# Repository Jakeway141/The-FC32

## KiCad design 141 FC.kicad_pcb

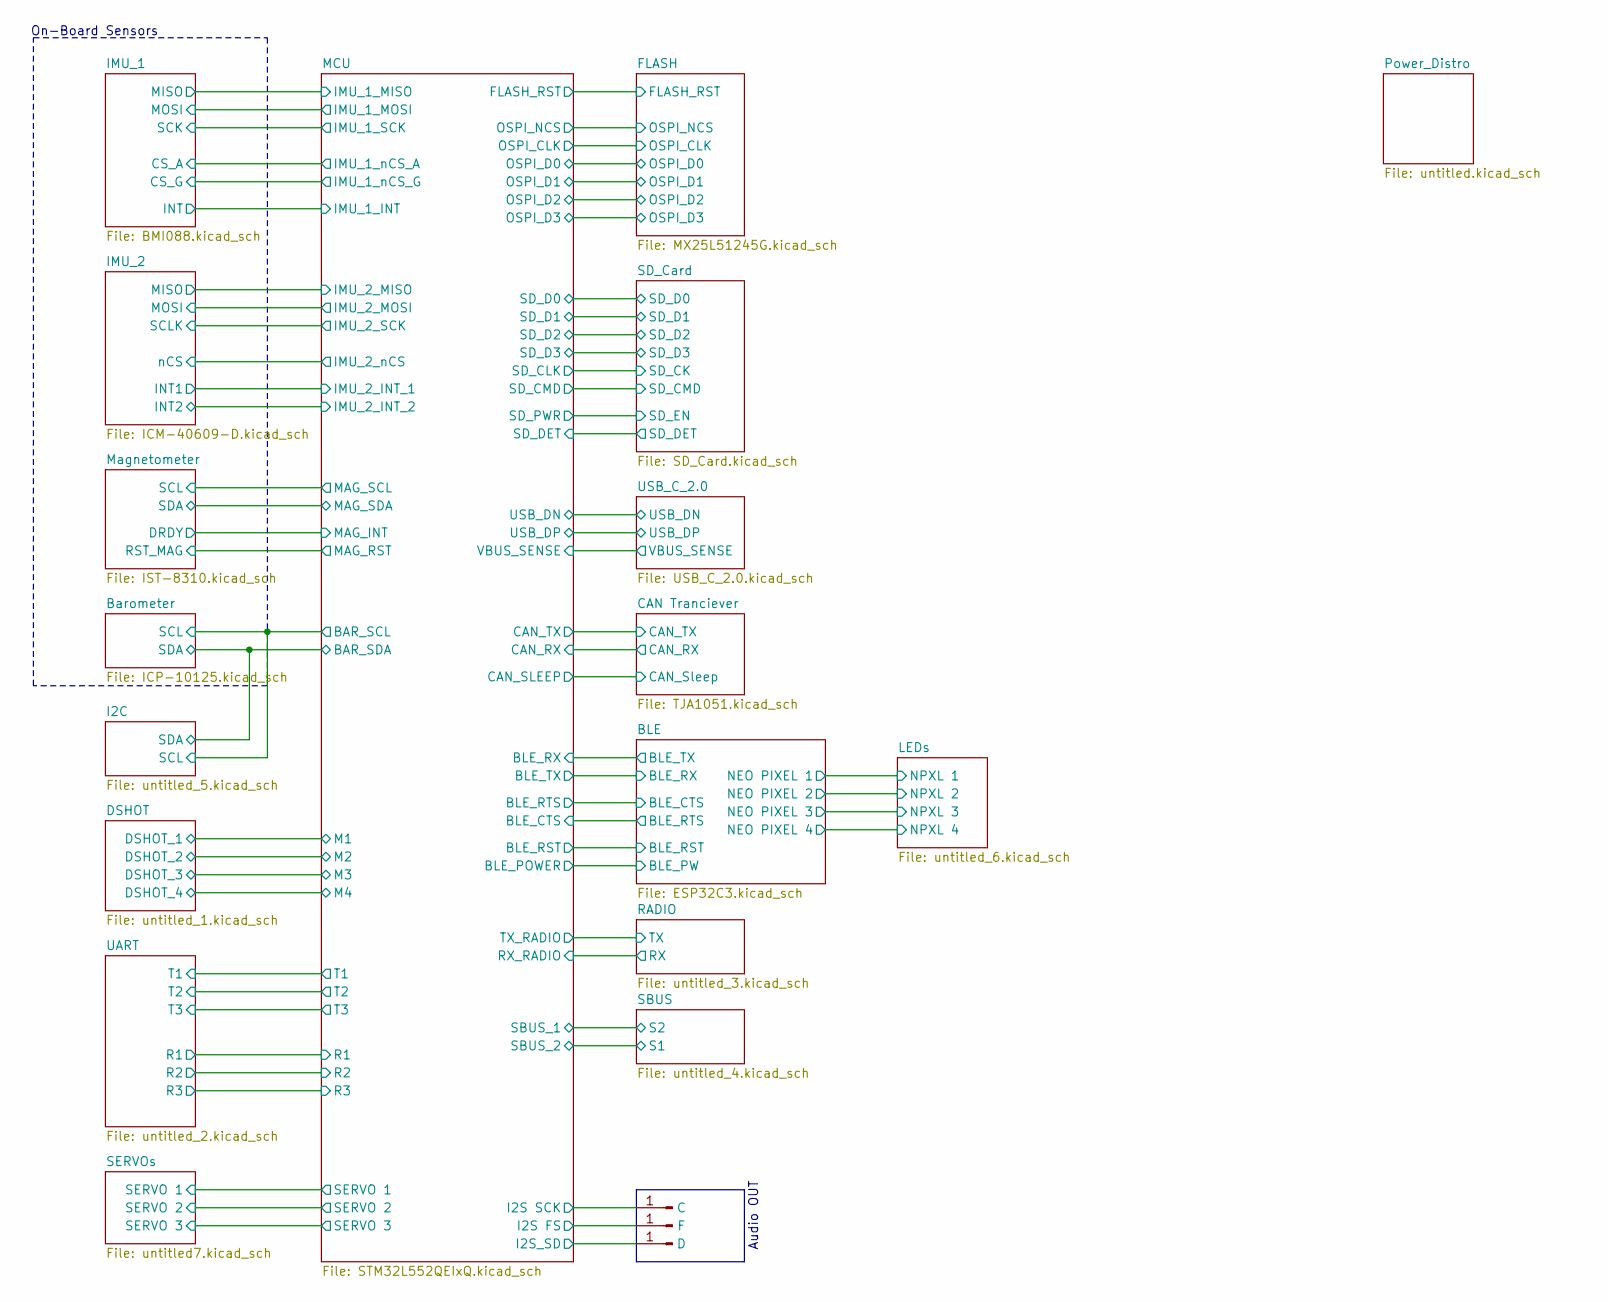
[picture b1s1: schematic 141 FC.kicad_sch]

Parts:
J47: C; SolderWirePad_1x01_SMD_1x2mm
J48: F; SolderWirePad_1x01_SMD_1x2mm
J49: D; SolderWirePad_1x01_SMD_1x2mm

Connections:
/MCU/I2S FS: J48.1 (Pin_1_1); also elsewhere on the board
/MCU/I2S SCK: J47.1 (Pin_1_1); also elsewhere on the board
/MCU/I2S_SD: J49.1 (Pin_1_1); also elsewhere on the board

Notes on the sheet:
Audio OUT
On-Board Sensors

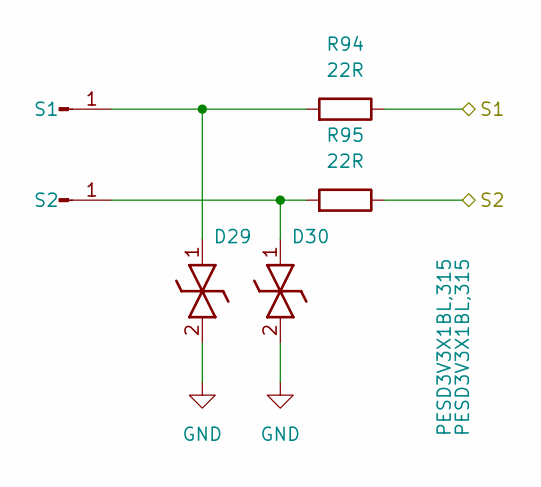
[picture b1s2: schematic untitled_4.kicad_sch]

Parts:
D29, D30: PESD3V3X1BL,315; PESD5V0S1BL315; Manufacturer_Part_Number PESD3V3X1BL,315; Mouser Part Number 771-PESD3V3X1BL,315
J59: S1; SolderWirePad_1x01_SMD_1x2mm
J60: S2; SolderWirePad_1x01_SMD_1x2mm
R94, R95: 22R; R_0805_2012Metric

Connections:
/MCU/SBUS_1: R95.1; also elsewhere on the board
/MCU/SBUS_2: R94.1; also elsewhere on the board
unnamed: D29.1 (K1), J59.1 (Pin_1_1), R94.2
unnamed: D30.1 (K1), J60.1 (Pin_1_1), R95.2

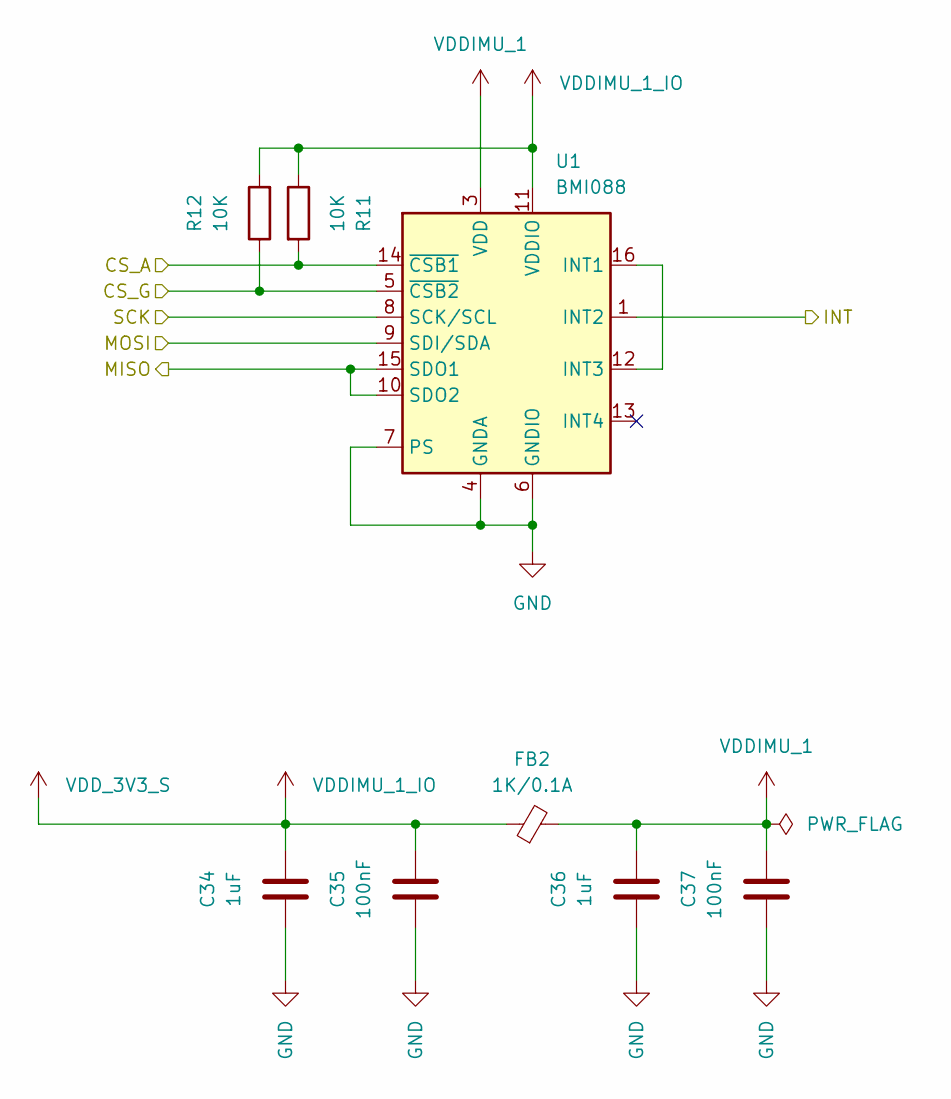
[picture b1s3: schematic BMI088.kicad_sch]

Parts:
C34, C36: 1uF; C_0603_1608Metric
C35, C37: 100nF; C_0603_1608Metric
FB2: 1K/0.1A; L_0603_1608Metric
R11, R12: 10K; R_0603_1608Metric
U1: BMI088; Bosch_LGA-16_4.5x3mm_P0.5mm_LayoutBorder7x1y_ClockwisePinNu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

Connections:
/IMU_1/CS_A: R11.2, U1.14 (~CSB1); also elsewhere on the board
/IMU_1/CS_G: R12.1, U1.5 (~CSB2); also elsewhere on the board
/IMU_1/INT: U1.1 (INT2); also elsewhere on the board
/IMU_1/MISO: U1.10 (SDO2), U1.15 (SDO1); also elsewhere on the board
/IMU_1/MOSI: U1.9 (SDI/SDA); also elsewhere on the board
/IMU_1/SCK: U1.8 (SCK/SCL); also elsewhere on the board
unnamed: U1.12 (INT3), U1.16 (INT1)
VDDIMU_1: C36.2, C37.2, FB2.2, U1.3 (VDD)
VDDIMU_1_IO: C34.2, C35.2, FB2.1, R11.1, R12.2, U1.11 (VDDIO); also elsewhere on the board

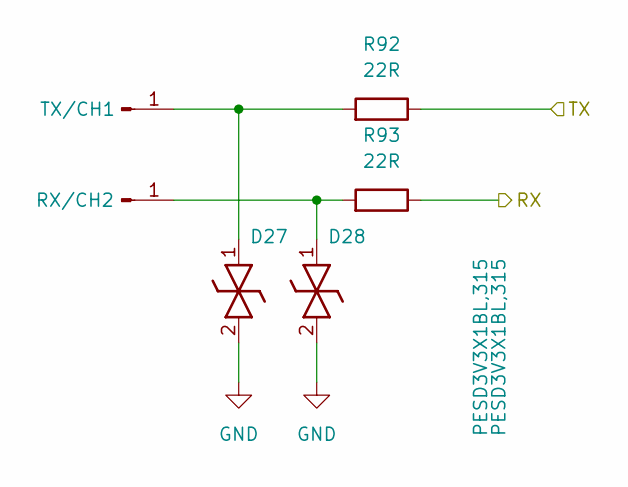
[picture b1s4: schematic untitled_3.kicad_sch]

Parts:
D27, D28: PESD3V3X1BL,315; PESD5V0S1BL315; Manufacturer_Part_Number PESD3V3X1BL,315; Mouser Part Number 771-PESD3V3X1BL,315
J61: TX/CH1; SolderWirePad_1x01_SMD_1x2mm
J62: RX/CH2; SolderWirePad_1x01_SMD_1x2mm
R92, R93: 22R; R_0805_2012Metric

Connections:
/MCU/RX_RADIO: R93.1; also elsewhere on the board
/MCU/TX_RADIO: R92.1; also elsewhere on the board
unnamed: D27.1 (K1), J61.1 (Pin_1_1), R92.2
unnamed: D28.1 (K1), J62.1 (Pin_1_1), R93.2

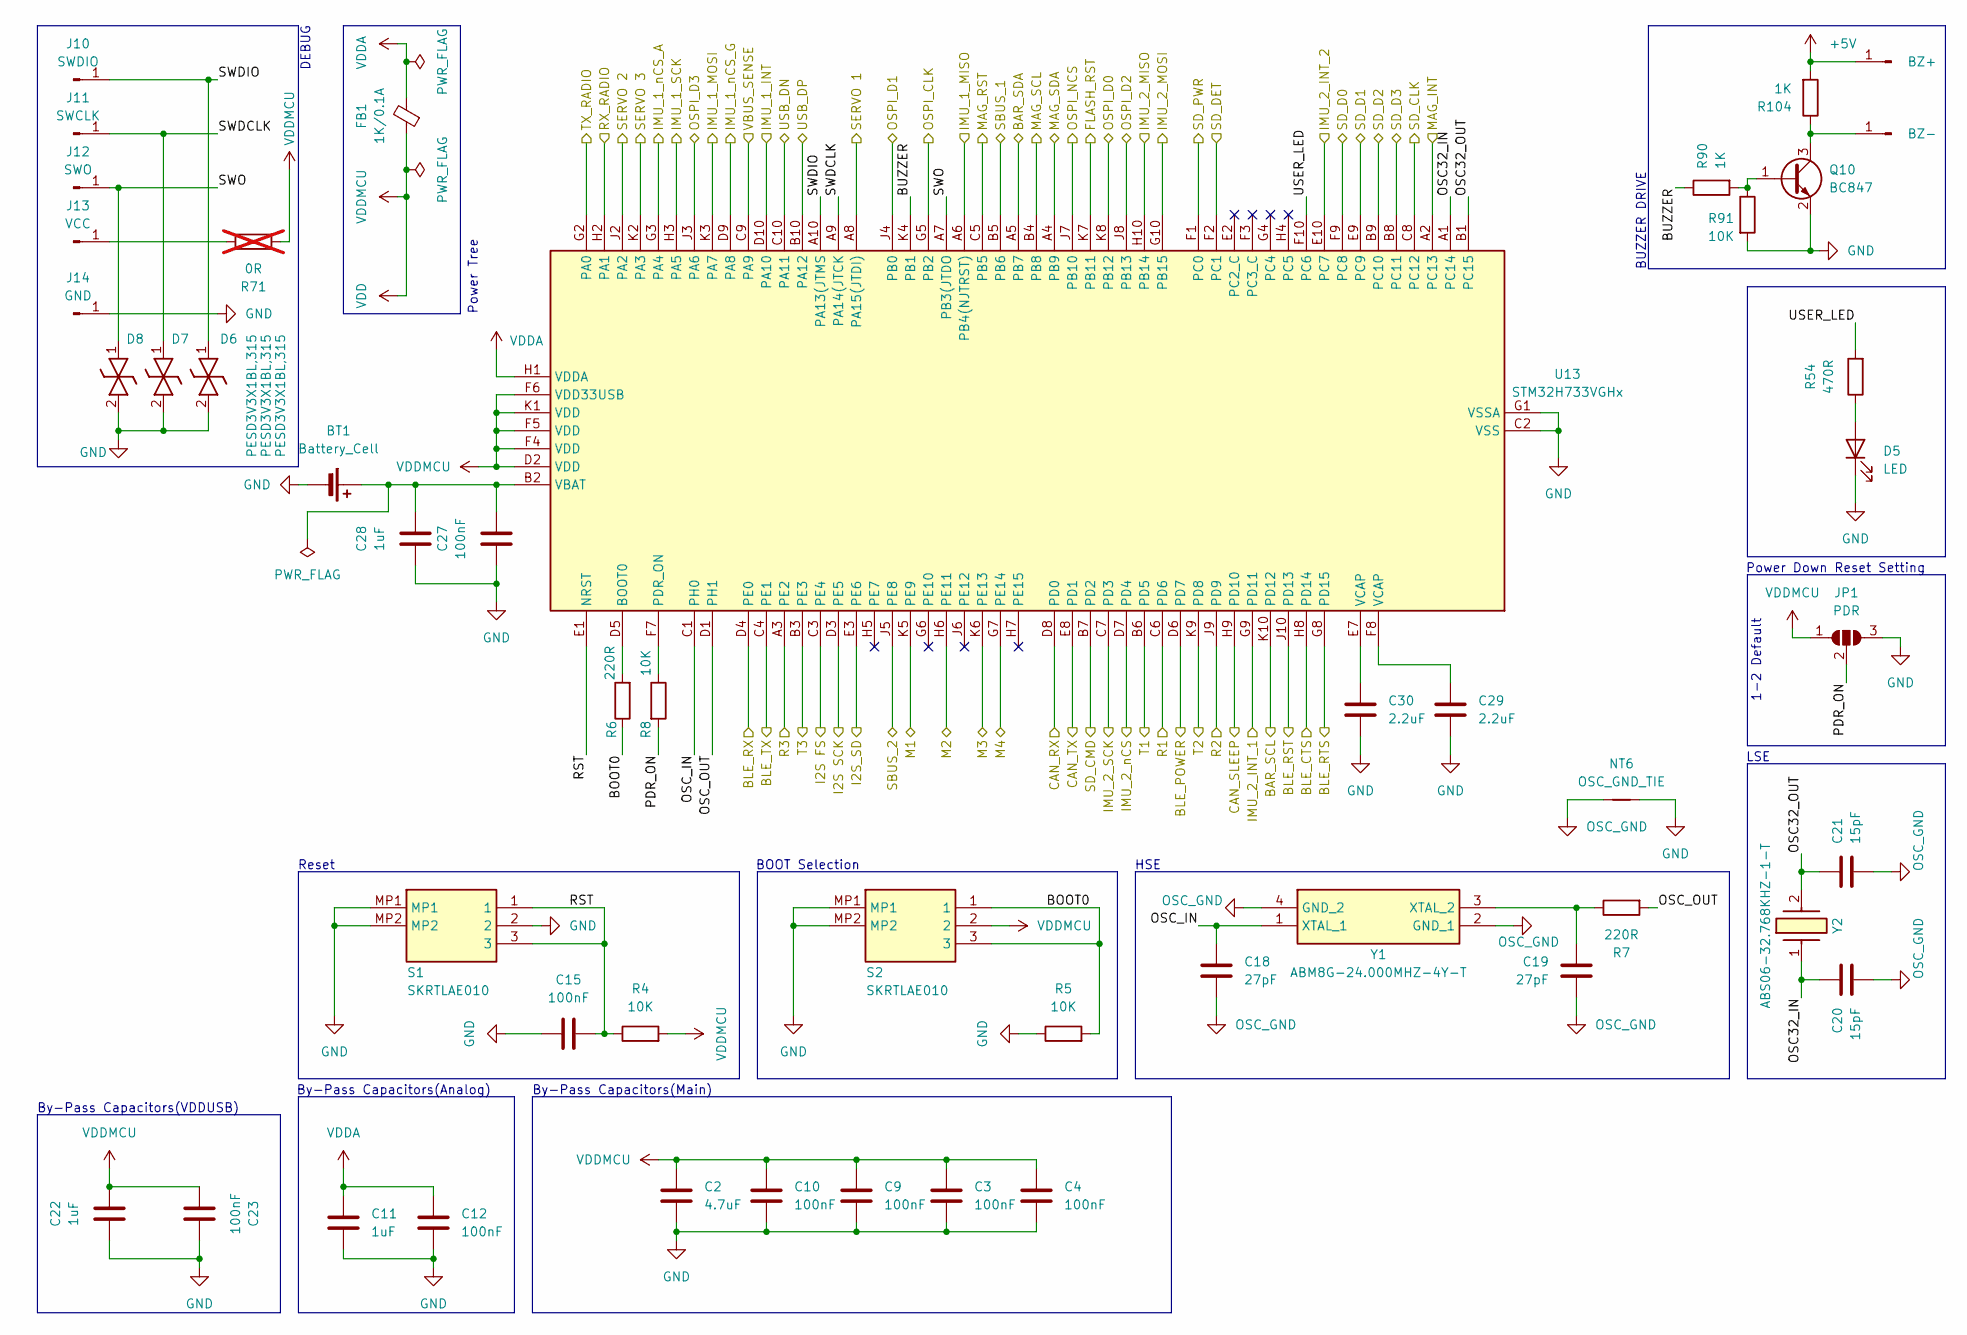
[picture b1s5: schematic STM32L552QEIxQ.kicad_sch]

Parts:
BT1: Battery_Cell; BatteryHolder_Keystone_3000_1x12mm
C2: 4.7uF; C_0603_1608Metric
C3, C4, C9, C10, C12, C15, C23, C27: 100nF; C_0603_1608Metric
C11, C22, C28: 1uF; C_0603_1608Metric
C18, C19: 27pF; C_0603_1608Metric
C20, C21: 15pF; C_0603_1608Metric
C29, C30: 2.2uF; C_0603_1608Metric
D5: LED; LED_0805_2012Metric
D6, D7, D8: PESD3V3X1BL,315; PESD5V0S1BL315; Manufacturer_Part_Number PESD3V3X1BL,315; Mouser Part Number 771-PESD3V3X1BL,315
FB1: 1K/0.1A; L_0603_1608Metric
J10: SWDIO; SolderWirePad_1x01_SMD_1x2mm
J11: SWCLK; SolderWirePad_1x01_SMD_1x2mm
J12: SWO; SolderWirePad_1x01_SMD_1x2mm
J13: VCC; SolderWirePad_1x01_SMD_1x2mm
J14: GND; SolderWirePad_1x01_SMD_1x2mm
J69: BZ+; SolderWirePad_1x01_SMD_1x2mm
J70: BZ-; SolderWirePad_1x01_SMD_1x2mm
JP1: PDR; SolderJumper-3_P2.0mm_Open_TrianglePad1.0x1.5mm_NumberLabels
NT6: OSC_GND_TIE; NetTie-2_SMD_Pad0.5mm
Q10: BC847; SOT-23
R4, R5, R8: 10K; R_0603_1608Metric
R6, R7: 220R; R_0603_1608Metric
R54: 470R; R_0603_1608Metric
R71: 0R; R_0805_2012Metric; not fitted
R90, R104: 1K; R_0805_2012Metric
R91: 10K; R_0805_2012Metric
S1, S2: SKRTLAE010; Manufacturer_Part_Number SKRTLAE010; Mouser Part Number 688-SKRTLA
U13: STM32H733VGHx; TFBGA-100_8x8mm_Layout10x10_P0.8mm
Y1: ABM8G-24.000MHZ-4Y-T; ABM8G; Manufacturer_Part_Number ABM8G-24.000MHZ-4Y-T
Y2: ABS06-32.768KHZ-1-T; ABS06; Manufacturer_Part_Number ABS06-32.768KHZ-1-T; Mouser Part Number 815-ABS06-32.7K-1-T

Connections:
/BLE/BLE_CTS: U13.G8 (PD15); also elsewhere on the board
/BLE/BLE_PW: U13.D6 (PD7); also elsewhere on the board
/BLE/BLE_RTS: U13.H8 (PD14); also elsewhere on the board
/BLE/BLE_RX: U13.C4 (PE1); also elsewhere on the board
/BLE/BLE_TX: U13.D4 (PE0); also elsewhere on the board
/BLE/CHIP_PU: U13.J10 (PD13); also elsewhere on the board
/Barometer/SCL: U13.K10 (PD12); also elsewhere on the board
/Barometer/SDA: U13.A5 (PB7); also elsewhere on the board
/CAN Tranciever/CAN_RX: U13.D8 (PD0); also elsewhere on the board
/CAN Tranciever/CAN_Sleep: U13.H9 (PD10); also elsewhere on the board
/CAN Tranciever/CAN_TX: U13.E8 (PD1); also elsewhere on the board
/DSHOT/DSHOT_1: U13.K5 (PE9); also elsewhere on the board
/DSHOT/DSHOT_2: U13.H6 (PE11); also elsewhere on the board
/DSHOT/DSHOT_3: U13.K6 (PE13); also elsewhere on the board
/DSHOT/DSHOT_4: U13.G7 (PE14); also elsewhere on the board
/FLASH/FLASH_RST: U13.K7 (PB11); also elsewhere on the board
/FLASH/OSPI_CLK: U13.G5 (PB2); also elsewhere on the board
/FLASH/OSPI_D0: U13.K8 (PB12); also elsewhere on the board
/FLASH/OSPI_D1: U13.J4 (PB0); also elsewhere on the board
/FLASH/OSPI_D2: U13.J8 (PB13); also elsewhere on the board
/FLASH/OSPI_D3: U13.J3 (PA6); also elsewhere on the board
/FLASH/OSPI_NCS: U13.J7 (PB10); also elsewhere on the board
/IMU_1/CS_A: U13.G3 (PA4); also elsewhere on the board
/IMU_1/CS_G: U13.D9 (PA8); also elsewhere on the board
/IMU_1/INT: U13.D10 (PA10); also elsewhere on the board
/IMU_1/MISO: U13.A6 (PB4(NJTRST)); also elsewhere on the board
/IMU_1/MOSI: U13.K3 (PA7); also elsewhere on the board
/IMU_1/SCK: U13.H3 (PA5); also elsewhere on the board
/IMU_2/INT1: U13.G9 (PD11); also elsewhere on the board
/IMU_2/INT2/FSYNC: U13.E10 (PC7); also elsewhere on the board
/IMU_2/MOSI: U13.G10 (PB15); also elsewhere on the board
/IMU_2/SCLK: U13.C7 (PD3); also elsewhere on the board
/IMU_2/SDO: U13.H10 (PB14); also elsewhere on the board
/IMU_2/nCS: U13.D7 (PD4); also elsewhere on the board
/MCU/BOOT0: R5.2, R6.1, S2.1, S2.3
/MCU/BUZZER: R90.1, U13.K4 (PB1)
/MCU/I2S FS: U13.C3 (PE4); also elsewhere on the board
/MCU/I2S SCK: U13.D3 (PE5); also elsewhere on the board
/MCU/I2S_SD: U13.E3 (PE6); also elsewhere on the board
/MCU/MAG_INT: U13.A2 (PC13); also elsewhere on the board
/MCU/MAG_RST: U13.C5 (PB5); also elsewhere on the board
/MCU/MAG_SCL: U13.B4 (PB8); also elsewhere on the board
/MCU/MAG_SDA: U13.A4 (PB9); also elsewhere on the board
/MCU/OSC32_IN: C20.1, U13.A1 (PC14), Y2.1
/MCU/OSC32_OUT: C21.1, U13.B1 (PC15), Y2.2
/MCU/OSC_IN: C18.1, U13.C1 (PH0), Y1.1 (XTAL_1)
/MCU/OSC_OUT: R7.2, U13.D1 (PH1)
/MCU/PDR_ON: JP1.2 (C), R8.2
/MCU/R1: U13.C6 (PD6); also elsewhere on the board
/MCU/R2: U13.J9 (PD9); also elsewhere on the board
/MCU/R3: U13.A3 (PE2); also elsewhere on the board
/MCU/RST: C15.2, R4.1, S1.1, S1.3, U13.E1 (NRST)
/MCU/RX_RADIO: U13.H2 (PA1); also elsewhere on the board
/MCU/SBUS_1: U13.B5 (PB6); also elsewhere on the board
/MCU/SBUS_2: U13.J5 (PE8); also elsewhere on the board
/MCU/SERVO 1: U13.A8 (PA15(JTDI)); also elsewhere on the board
/MCU/SERVO 2: U13.J2 (PA2); also elsewhere on the board
/MCU/SERVO 3: U13.K2 (PA3); also elsewhere on the board
/MCU/SWDCLK: D7.1 (K1), J11.1 (Pin_1_1), U13.A9 (PA14(JTCK)
/MCU/SWDIO: D6.1 (K1), J10.1 (Pin_1_1), U13.A10 (PA13(JTMS)
/MCU/SWO: D8.1 (K1), J12.1 (Pin_1_1), U13.A7 (PB3(JTDO)
/MCU/T1: U13.B6 (PD5); also elsewhere on the board
/MCU/T2: U13.K9 (PD8); also elsewhere on the board
/MCU/T3: U13.B3 (PE3); also elsewhere on the board
/MCU/TX_RADIO: U13.G2 (PA0); also elsewhere on the board
/MCU/USB_DN: U13.C10 (PA11); also elsewhere on the board
/MCU/USB_DP: U13.B10 (PA12); also elsewhere on the board
/MCU/USER_LED: R54.2, U13.F10 (PC6)
/MCU/VBUS_SENSE: U13.C9 (PA9); also elsewhere on the board
/SD_Card/OUT_CLK: U13.C8 (PC12); also elsewhere on the board
/SD_Card/OUT_CMD: U13.B7 (PD2); also elsewhere on the board
/SD_Card/OUT_D0: U13.F9 (PC8); also elsewhere on the board
/SD_Card/OUT_D1: U13.E9 (PC9); also elsewhere on the board
/SD_Card/OUT_D2: U13.B9 (PC10); also elsewhere on the board
/SD_Card/OUT_D3: U13.B8 (PC11); also elsewhere on the board
/SD_Card/uSD_DET: U13.F2 (PC1); also elsewhere on the board
/SD_Card/uSD_Rail_Ctrl: U13.F1 (PC0); also elsewhere on the board
unnamed: BT1.1 (+), C27.1, C28.2, U13.B2 (VBAT)
unnamed: C29.2, U13.F8 (VCAP)
unnamed: C30.2, U13.E7 (VCAP)
unnamed: D5.2 (A), R54.1
unnamed: J13.1 (Pin_1_1), R71.1
unnamed: R6.2, U13.D5 (BOOT0)
unnamed: R8.1, U13.F7 (PDR_ON)
unnamed: C19.1, R7.1, Y1.3 (XTAL_2)
OSC_GND: C18.2, C19.2, C20.2, C21.2, NT6.2, Y1.2 (GND_1), Y1.4 (GND_2)
VDD: C2.1, C3.1, C4.1, C9.1, C10.1, C22.2, C23.2, FB1.1, JP1.1 (A), R4.2, R71.2, S2.2, U13.D2 (VDD), U13.F4 (VDD), U13.F5 (VDD), U13.F6 (VDD33USB), U13.K1 (VDD); also elsewhere on the board
VDDA: C11.1, C12.1, FB1.2, U13.H1 (VDDA)

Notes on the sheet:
Power Tree
1-2 Default
DEBUG
BOOT Selection
By-Pass Capacitors(VDDUSB)
Reset
LSE
Power Down Reset Setting
HSE
BUZZER DRIVE
By-Pass Capacitors(Main)
By-Pass Capacitors(Analog)

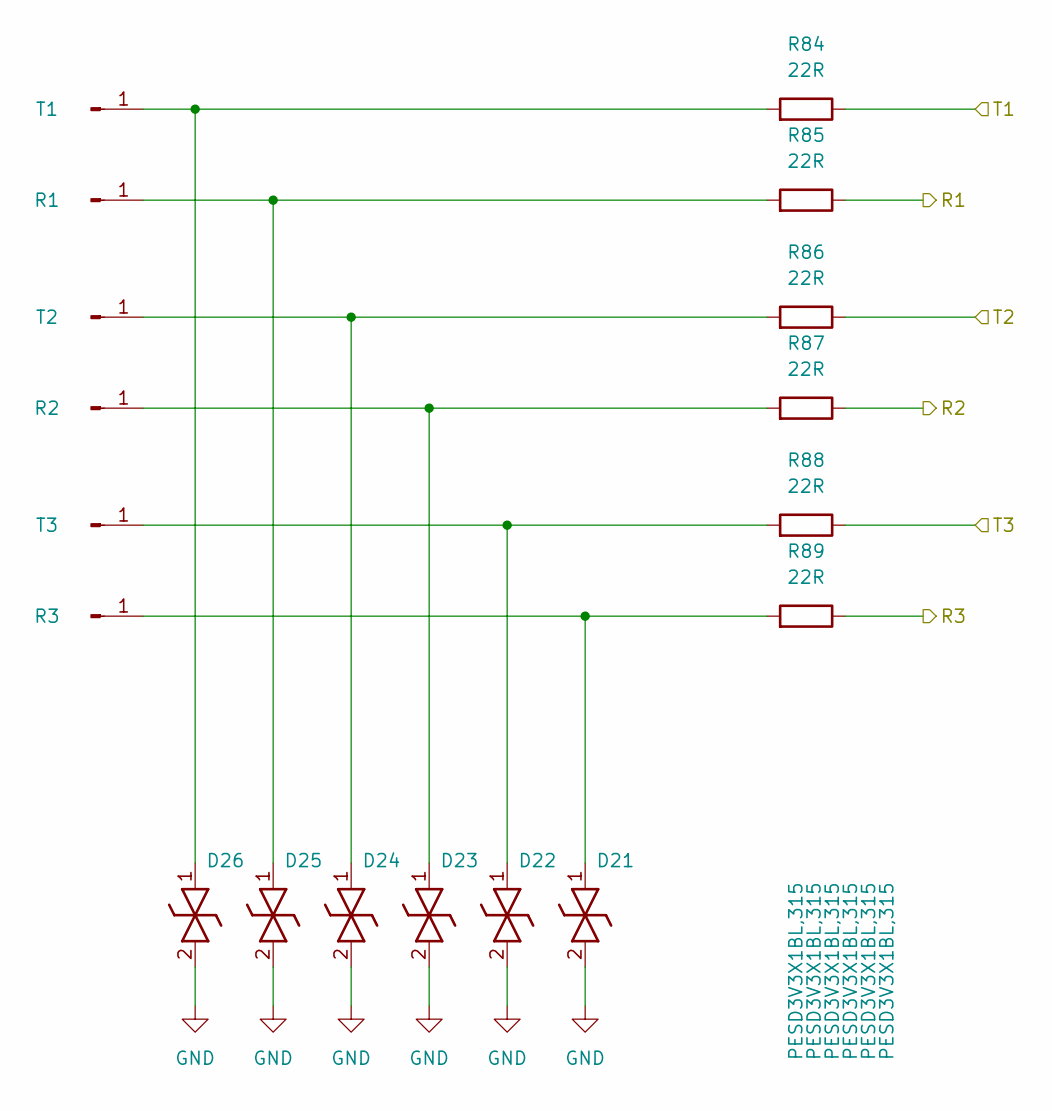
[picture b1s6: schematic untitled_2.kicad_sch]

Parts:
D21, D22, D23, D24, D25, D26: PESD3V3X1BL,315; PESD5V0S1BL315; Manufacturer_Part_Number PESD3V3X1BL,315; Mouser Part Number 771-PESD3V3X1BL,315
J63: T1; SolderWirePad_1x01_SMD_1x2mm
J64: R1; SolderWirePad_1x01_SMD_1x2mm
J65: T2; SolderWirePad_1x01_SMD_1x2mm
J66: R2; SolderWirePad_1x01_SMD_1x2mm
J67: T3; SolderWirePad_1x01_SMD_1x2mm
J68: R3; SolderWirePad_1x01_SMD_1x2mm
R84, R85, R86, R87, R88, R89: 22R; R_0805_2012Metric

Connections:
/MCU/R1: R85.1; also elsewhere on the board
/MCU/R2: R87.1; also elsewhere on the board
/MCU/R3: R89.1; also elsewhere on the board
/MCU/T1: R84.1; also elsewhere on the board
/MCU/T2: R86.1; also elsewhere on the board
/MCU/T3: R88.1; also elsewhere on the board
unnamed: D21.1 (K1), J68.1 (Pin_1_1), R89.2
unnamed: D22.1 (K1), J67.1 (Pin_1_1), R88.2
unnamed: D23.1 (K1), J66.1 (Pin_1_1), R87.2
unnamed: D24.1 (K1), J65.1 (Pin_1_1), R86.2
unnamed: D25.1 (K1), J64.1 (Pin_1_1), R85.2
unnamed: D26.1 (K1), J63.1 (Pin_1_1), R84.2

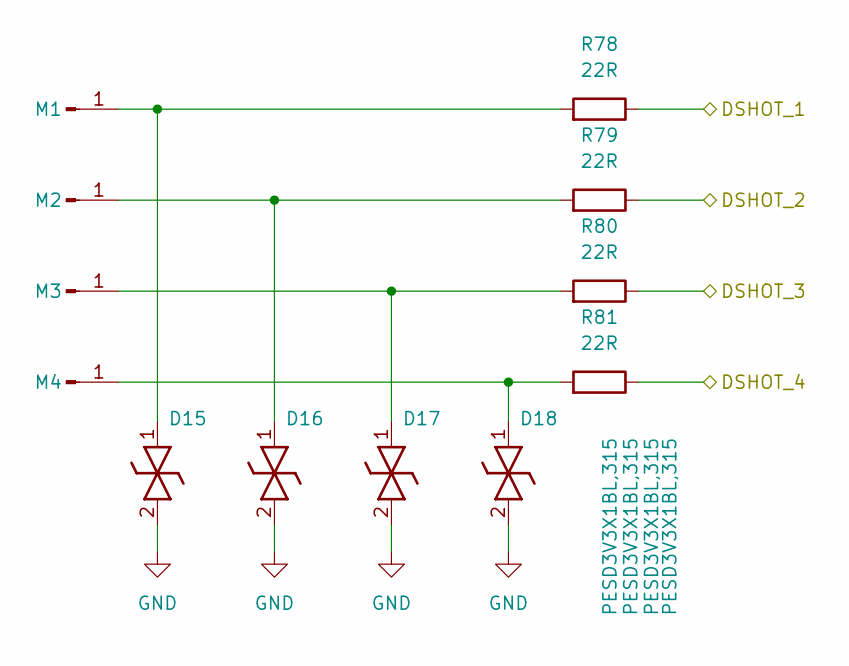
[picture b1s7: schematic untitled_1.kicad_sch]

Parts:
D15, D16, D17, D18: PESD3V3X1BL,315; PESD5V0S1BL315; Manufacturer_Part_Number PESD3V3X1BL,315; Mouser Part Number 771-PESD3V3X1BL,315
J71: M1; SolderWirePad_1x01_SMD_1x2mm
J72: M2; SolderWirePad_1x01_SMD_1x2mm
J73: M3; SolderWirePad_1x01_SMD_1x2mm
J74: M4; SolderWirePad_1x01_SMD_1x2mm
R78, R79, R80, R81: 22R; R_0805_2012Metric

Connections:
/DSHOT/DSHOT_1: R78.1; also elsewhere on the board
/DSHOT/DSHOT_2: R79.1; also elsewhere on the board
/DSHOT/DSHOT_3: R80.1; also elsewhere on the board
/DSHOT/DSHOT_4: R81.1; also elsewhere on the board
unnamed: D15.1 (K1), J71.1 (Pin_1_1), R78.2
unnamed: D16.1 (K1), J72.1 (Pin_1_1), R79.2
unnamed: D17.1 (K1), J73.1 (Pin_1_1), R80.2
unnamed: D18.1 (K1), J74.1 (Pin_1_1), R81.2

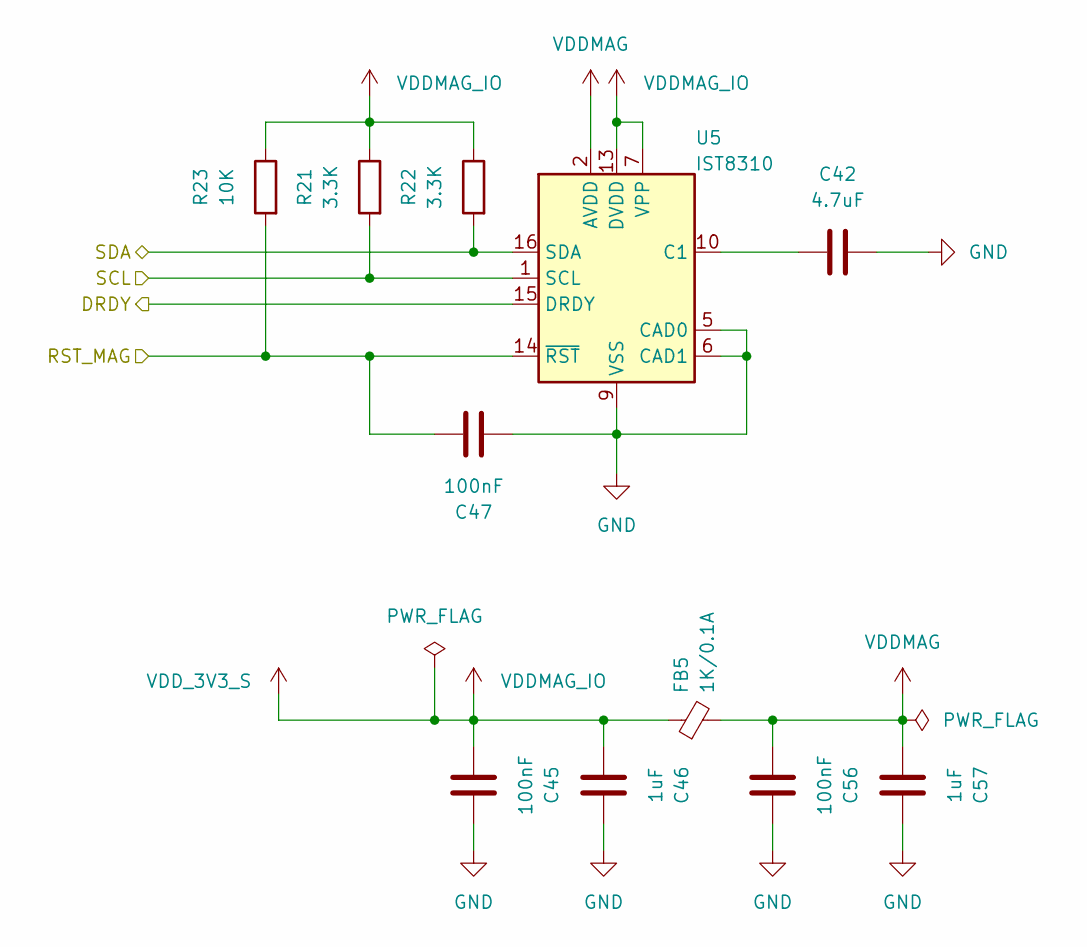
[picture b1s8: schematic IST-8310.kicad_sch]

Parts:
C42: 4.7uF; C_0603_1608Metric
C45, C47, C56: 100nF; C_0603_1608Metric
C46, C57: 1uF; C_0603_1608Metric
FB5: 1K/0.1A; L_0603_1608Metric
R21, R22: 3.3K; R_0603_1608Metric
R23: 10K; R_0603_1608Metric
U5: IST8310; LGA-16_3x3mm_P0.5mm

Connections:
/MCU/MAG_INT: U5.15 (DRDY); also elsewhere on the board
/MCU/MAG_RST: C47.2, R23.2, U5.14 (~RST); also elsewhere on the board
/MCU/MAG_SCL: R21.2, U5.1 (SCL); also elsewhere on the board
/MCU/MAG_SDA: R22.2, U5.16 (SDA); also elsewhere on the board
unnamed: C42.1, U5.10 (C1)
VDDIMU_1_IO: C45.2, C46.2, FB5.1, R21.1, R22.1, R23.1, U5.7 (VPP), U5.13 (DVDD); also elsewhere on the board
VDDMAG: C56.2, C57.2, FB5.2, U5.2 (AVDD)

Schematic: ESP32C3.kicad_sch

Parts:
C49: 100nF; C_0603_1608Metric
C73: 10uF; C_0603_1608Metric
C74: 1uF; C_0603_1608Metric
D2, D3: LED; LED_0805_2012Metric
D10, D11, D12, D13, D14: PESD3V3X1BL,315; PESD5V0S1BL315; Manufacturer_Part_Number PESD3V3X1BL,315; Mouser Part Number 771-PESD3V3X1BL,315
J4: DTR; SolderWirePad_1x01_SMD_1x2mm
J5: TXD; SolderWirePad_1x01_SMD_1x2mm
J6: RXD; SolderWirePad_1x01_SMD_1x2mm
J7: VCC; SolderWirePad_1x01_SMD_1x2mm
J8, J18: GND; SolderWirePad_1x01_SMD_1x2mm
J9: RTS; SolderWirePad_1x01_SMD_1x2mm
J15: VBUS; SolderWirePad_1x01_SMD_1x2mm
J16: DN; SolderWirePad_1x01_SMD_1x2mm
J17: DP; SolderWirePad_1x01_SMD_1x2mm
Q3: BC847BDW1; SOT-363_SC-70-6
Q4, Q8: BC847; SOT-23
Q5: FDN340P; SOT-23
R43, R44, R45, R46, R47, R51, R52, R68: 10K; R_0603_1608Metric
R48, R53: 470R; R_0603_1608Metric
R49, R67: 1K; R_0603_1608Metric
R50: 47K; R_0603_1608Metric
R69: 0R; R_0603_1608Metric; not fitted
R70: 0R; R_0805_2012Metric; not fitted
TP1: VDDBLE; TestPoint_Pad_D1.5mm
U9: ESP32-C6-MINI-1

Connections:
/BLE/BLE_CTS: U9.10 (IO5); also elsewhere on the board
/BLE/BLE_PW: R49.1; also elsewhere on the board
/BLE/BLE_RTS: U9.9 (IO4); also elsewhere on the board
/BLE/BLE_RX: U9.15 (IO6); also elsewhere on the board
/BLE/BLE_TX: U9.16 (IO7); also elsewhere on the board
/BLE/CHIP_PU: C74.2, Q3.6 (C1), R43.1, U9.8 (EN); also elsewhere on the board
/BLE/DN: J16.1 (Pin_1_1), U9.17 (IO12)
/BLE/DP: J17.1 (Pin_1_1), U9.18 (IO13)
/BLE/DTR: D14.1 (K1), J4.1 (Pin_1_1), Q3.4 (E2), R47.2
/BLE/GPIO_8: D2.1 (K), R44.1, U9.22 (IO8)
/BLE/GPIO_9: Q3.3 (C2), R45.1, U9.23 (IO9)
/BLE/NEO PIXEL 1: U9.24 (IO18); also elsewhere on the board
/BLE/NEO PIXEL 2: U9.25 (IO19); also elsewhere on the board
/BLE/NEO PIXEL 3: U9.26 (IO20); also elsewhere on the board
/BLE/NEO PIXEL 4: U9.27 (IO21); also elsewhere on the board
/BLE/RTS: D10.1 (K1), J9.1 (Pin_1_1), Q3.1 (E1), R46.1
/BLE/RXD: D12.1 (K1), J6.1 (Pin_1_1), U9.30 (RXD0)
/BLE/TXD: D13.1 (K1), J5.1 (Pin_1_1), U9.31 (TXD0)
/BLE/VBUS_SENSE: Q8.3 (C), R68.2, U9.19 (IO14)
unnamed: D2.2 (A), R48.1
unnamed: D3.2 (A), R53.2
unnamed: D11.1 (K1), J7.1 (Pin_1_1), R70.2
unnamed: J15.1 (Pin_1_1), R67.2
unnamed: Q3.2 (B1), R47.1
unnamed: Q3.5 (B2), R46.2
unnamed: Q4.1 (B), R49.2, R51.1
unnamed: Q4.3 (C), R52.2
unnamed: Q5.1 (G), R50.2, R52.1
unnamed: Q8.1 (B), R67.1
VDD: Q5.2 (S), R50.1, R69.2; also elsewhere on the board
VDDBLE: C49.2, C73.2, Q5.3 (D), R43.2, R44.2, R45.2, R48.2, R53.1, R68.1, R69.1, R70.1, TP1.1 (1_1), U9.3 (3V3)

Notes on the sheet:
USB
Chip Pull-Up
By-Pass Capacitors
Populate R61 for BLE always ON & remove everything else.
LED_BUILT_IN
FLASH
Power Tree
Auto Download

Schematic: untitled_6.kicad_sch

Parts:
D33, D34, D35, D36: PESD3V3X1BL,315; PESD5V0S1BL315; Manufacturer_Part_Number PESD3V3X1BL,315; Mouser Part Number 771-PESD3V3X1BL,315
J53: L1; SolderWirePad_1x01_SMD_1x2mm
J54: L2; SolderWirePad_1x01_SMD_1x2mm
J55: L3; SolderWirePad_1x01_SMD_1x2mm
J56: L4; SolderWirePad_1x01_SMD_1x2mm
R100, R101, R102, R103: 22R; R_0805_2012Metric

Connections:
/BLE/NEO PIXEL 1: R100.1; also elsewhere on the board
/BLE/NEO PIXEL 2: R101.1; also elsewhere on the board
/BLE/NEO PIXEL 3: R102.1; also elsewhere on the board
/BLE/NEO PIXEL 4: R103.1; also elsewhere on the board
unnamed: D33.1 (K1), J53.1 (Pin_1_1), R100.2
unnamed: D34.1 (K1), J54.1 (Pin_1_1), R101.2
unnamed: D35.1 (K1), J55.1 (Pin_1_1), R102.2
unnamed: D36.1 (K1), J56.1 (Pin_1_1), R103.2

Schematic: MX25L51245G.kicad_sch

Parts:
C31: 4.7uF; C_0603_1608Metric
C32, C33: 100nF; C_0603_1608Metric
IC1: MX25L51245GXDI-08G; BGA24C100P5X5_600X800X120; Manufacturer_Part_Number MX25L51245GXDI-08G
R9, R10: 10K; R_0603_1608Metric

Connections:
/FLASH/FLASH_RST: C33.2, IC1.A4 (RESET#), R9.1; also elsewhere on the board
/FLASH/OSPI_CLK: IC1.B2 (SCLK); also elsewhere on the board
/FLASH/OSPI_D0: IC1.D3 (SI/SIO0); also elsewhere on the board
/FLASH/OSPI_D1: IC1.D2 (SO/SIO1); also elsewhere on the board
/FLASH/OSPI_D2: IC1.C4 (WP#/SIO2); also elsewhere on the board
/FLASH/OSPI_D3: IC1.D4 (NC/SIO3); also elsewhere on the board
/FLASH/OSPI_NCS: IC1.C2 (CS#), R10.2; also elsewhere on the board
VDD: C31.2, C32.2, IC1.B4 (VCC), R9.2, R10.1; also elsewhere on the board

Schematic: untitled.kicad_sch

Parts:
C16, C17, C24, C77: 100uF/6.3V; CP_EIA-3528-12_Kemet-T
C48, C54: 1uF; C_0603_1608Metric
C50, C52, C67, C71: 100nF; C_0805_2012Metric
C51: 10nF; C_0805_2012Metric
C53, C62: 100nF; C_0603_1608Metric
C69, C72: 1uF; C_0805_2012Metric
C70: 100nF; C_0805_2012Metric; not fitted
D4: LED; LED_0805_2012Metric
D37: PTVS6V0S1UR,115; SOD123W; Manufacturer_Part_Number PTVS6V0S1UR,115; Mouser Part Number 771-PTVS6V0S1UR115
FB6: 60R/6A; L_1806_4516Metric
J20: GND; SolderWirePad_1x01_SMD_1.5x3mm
J21: +5V; SolderWirePad_1x01_SMD_1.5x3mm
L1: 74438334015; INDC3030X120N; Manufacturer_Part_Number 74438334015; Mouser Part Number 710-74438334015
Q6, Q7: BC847BDW1; SOT-363_SC-70-6
R24, R58, R72, R73, R74, R75: 10K; R_0805_2012Metric
R25, R37: 10K; R_0603_1608Metric
R40: 75K; R_0805_2012Metric
R41: 24K; R_0805_2012Metric
R42: 100R; R_0805_2012Metric; not fitted
R55, R56, R57, R59, R60: 1K; R_0805_2012Metric
U7: AP62300WU; TSOT-23-6
U10: NCP163ASN180T1G; SOT-23-5
U11: NCP163ASN330T1G; SOT-23-5

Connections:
/Power_Distro/FBX: R40.1, R41.2, U7.4 (FB)
unnamed: C50.2, C51.2, C69.2, FB6.1, L1.2, R40.2
unnamed: C70.1, R42.2
unnamed: D4.2 (A), Q7.3 (C2), R60.1
unnamed: Q6.2 (B1), R55.2, R72.2
unnamed: Q6.6 (C1), R58.1, R59.1
unnamed: Q6.1 (E1), Q6.3 (C2)
unnamed: Q6.5 (B2), R56.2, R74.2
unnamed: Q6.4 (E2), Q7.6 (C1)
unnamed: Q7.2 (B1), R57.2, R73.1
unnamed: Q7.5 (B2), R59.2, R75.2
unnamed: C67.1, U7.6 (BST)
unnamed: C52.2, R24.2, U7.5 (EN)
unnamed: C67.2, L1.1, U7.2 (SW)
unnamed: C62.1, R37.2, U10.3 (EN)
unnamed: C53.1, R25.2, U11.3 (EN)
VDD: C16.1, C70.2, C71.2, C72.2, FB6.2, R55.1; also elsewhere on the board
VDDIMU_1_IO: C17.1, R56.1, U11.5 (VOUT); also elsewhere on the board
VDD_1V8: C24.1, R57.1, U10.5 (VOUT); also elsewhere on the board

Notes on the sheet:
+5V IN
+3V3 Rail_Sensor
+1V8 Rail
Populate C70 & R42 when there's ringing on VDD
+3V3 Rail
Rail OK

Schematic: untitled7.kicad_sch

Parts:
D38, D39, D40: PESD3V3X1BL,315; PESD5V0S1BL315; Manufacturer_Part_Number PESD3V3X1BL,315; Mouser Part Number 771-PESD3V3X1BL,315
J50: SM1; SolderWirePad_1x01_SMD_1x2mm
J51: SM2; SolderWirePad_1x01_SMD_1x2mm
J52: SM3; SolderWirePad_1x01_SMD_1x2mm
R105, R106, R107: 22R; R_0805_2012Metric

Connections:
/MCU/SERVO 1: R105.1; also elsewhere on the board
/MCU/SERVO 2: R106.1; also elsewhere on the board
/MCU/SERVO 3: R107.1; also elsewhere on the board
unnamed: D38.1 (K1), J50.1 (Pin_1_1), R105.2
unnamed: D39.1 (K1), J51.1 (Pin_1_1), R106.2
unnamed: D40.1 (K1), J52.1 (Pin_1_1), R107.2

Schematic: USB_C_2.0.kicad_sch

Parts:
C76: 100nF; C_0603_1608Metric
D9: LED; LED_0805_2012Metric
J23: USB_C_Receptacle_USB2.0_16P; USB_C_Receptacle_GCT_USB4105-xx-A_16P_TopMnt_Horizontal
Q9: BC847; SOT-23
R61: 470R; R_0603_1608Metric
R62: 0R; R_0603_1608Metric
R63, R64: 5.1K; R_0603_1608Metric
R65: 33K; R_0603_1608Metric
R66: 82K; R_0603_1608Metric
R76: 10K; R_0603_1608Metric
R77: 1K; R_0603_1608Metric
U12: USBLC6-2SC6; SOT-23-6

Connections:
/MCU/USB_DN: U12.4 (I/O2); also elsewhere on the board
/MCU/USB_DP: U12.6 (I/O1); also elsewhere on the board
/MCU/VBUS_SENSE: R65.1, R66.2; also elsewhere on the board
/USB_C_2.0/D+_IN: J23.A6 (D+), J23.B6 (D+), U12.1 (I/O1)
/USB_C_2.0/D-_IN: J23.A7 (D-), J23.B7 (D-), U12.3 (I/O2)
unnamed: D9.2 (A), R61.1
unnamed: D9.1 (K), Q9.3 (C)
unnamed: J23.A5 (CC1), R63.2
unnamed: J23.B5 (CC2), R64.2
unnamed: J23.SH (SHIELD), R62.1
unnamed: Q9.1 (B), R76.1, R77.1
unnamed: C76.2, J23.A4 (VBUS), J23.A9 (VBUS), J23.B4 (VBUS), J23.B9 (VBUS), R65.2, R77.2, U12.5 (VBUS)

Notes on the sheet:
VBUS Indication

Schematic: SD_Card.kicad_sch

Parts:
C58: 1uF; C_0603_1608Metric
C66: 100nF; C_0603_1608Metric
D1: LED; LED_0805_2012Metric
IC4: EMIF06-HSD03F3; EMIF06HSD03F3; Mouser Part Number 511-EMIF06-HSD03F3
J1: Micro_SD_Card_Det_Hirose_DM3AT; microSD_HC_Hirose_DM3AT-SF-PEJM5
Q1: FDN340P; SOT-23
Q2: BC847; SOT-23
R26, R27, R28, R29, R30, R31, R32, R82: 47K; R_0603_1608Metric
R33, R34: 10K; R_0603_1608Metric
R35: 1K; R_0603_1608Metric
R36: 470R; R_0603_1608Metric

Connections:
/SD_Card/IN_CLK: IC4.E3 (I3), J1.5 (CLK)
/SD_Card/IN_CMD: IC4.G3 (I4), J1.3 (CMD)
/SD_Card/IN_D0: IC4.C3 (I2), J1.7 (DAT0)
/SD_Card/IN_D1: IC4.A3 (I1), J1.8 (DAT1)
/SD_Card/IN_D2: IC4.K3 (I6), J1.1 (DAT2)
/SD_Card/IN_D3: IC4.I3 (I5), J1.2 (DAT3/CD)
/SD_Card/OUT_CLK: IC4.E1 (O3), R82.2; also elsewhere on the board
/SD_Card/OUT_CMD: IC4.G1 (O4), R30.2; also elsewhere on the board
/SD_Card/OUT_D0: IC4.C1 (O2), R26.2; also elsewhere on the board
/SD_Card/OUT_D1: IC4.A1 (O1), R27.2; also elsewhere on the board
/SD_Card/OUT_D2: IC4.K1 (O6), R28.2; also elsewhere on the board
/SD_Card/OUT_D3: IC4.I1 (O5), R29.2; also elsewhere on the board
/SD_Card/uSD_DET: IC4.J2 (DET), J1.10 (DET_A), R31.2; also elsewhere on the board
/SD_Card/uSD_Rail_Ctrl: R35.1; also elsewhere on the board
unnamed: D1.2 (A), R36.2
unnamed: Q1.1 (G), R32.2, R33.1
unnamed: Q2.1 (B), R34.1, R35.2
unnamed: Q2.3 (C), R33.2
VDD: Q1.2 (S), R31.1, R32.1; also elsewhere on the board
VDD_SD: C58.2, C66.2, IC4.B2 (VCC), J1.4 (VDD), Q1.3 (D), R26.1, R27.1, R28.1, R29.1, R30.1, R36.1, R82.1

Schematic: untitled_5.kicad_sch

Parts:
D31, D32: PESD3V3X1BL,315; PESD5V0S1BL315; Manufacturer_Part_Number PESD3V3X1BL,315; Mouser Part Number 771-PESD3V3X1BL,315
J57: SCL; SolderWirePad_1x01_SMD_1x2mm
J58: SDA; SolderWirePad_1x01_SMD_1x2mm
R96, R97: 22R; R_0805_2012Metric
R98, R99: 10K; R_0805_2012Metric

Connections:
/Barometer/SCL: R96.1; also elsewhere on the board
/Barometer/SDA: R97.1; also elsewhere on the board
unnamed: D31.1 (K1), J57.1 (Pin_1_1), R96.2, R98.2
unnamed: D32.1 (K1), J58.1 (Pin_1_1), R97.2, R99.2
VDD: R98.1, R99.1; also elsewhere on the board

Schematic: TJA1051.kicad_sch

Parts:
C59: 100nF; C_0805_2012Metric
C60: 47nF; C_0805_2012Metric
C63, C64: 100pF; C_0805_2012Metric
C65: 4.7nF; C_0805_2012Metric
C68: 1uF; C_0805_2012Metric
J2: CAN_H; SolderWirePad_1x01_SMD_1.5x3mm
J3: CAN_L; SolderWirePad_1x01_SMD_1.5x3mm
J19: GND; SolderWirePad_1x01_SMD_1.5x3mm
R38, R39: 1.3K; R_0805_2012Metric
U8: TJA1051TK-3; HVSON-8-1EP_3x3mm_P0.65mm_EP1.6x2.4mm

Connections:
/CAN Tranciever/CAN_RX: U8.4 (RXD); also elsewhere on the board
/CAN Tranciever/CAN_Sleep: U8.8 (S); also elsewhere on the board
/CAN Tranciever/CAN_TX: U8.1 (TXD); also elsewhere on the board
unnamed: C65.2, R38.2, R39.1
unnamed: C63.2, J2.1 (Pin_1_1), R38.1, U8.7 (CANH)
unnamed: C64.1, J3.1 (Pin_1_1), R39.2, U8.6 (CANL)
VDD: C59.1, U8.5 (VIO); also elsewhere on the board

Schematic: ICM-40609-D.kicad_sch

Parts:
C38: 2.2uF; C_0603_1608Metric
C39: 100nF; C_0603_1608Metric
C40: 10nF; C_0603_1608Metric
FB3: 1K/0.1A; L_0603_1608Metric
R13: 10K; R_0603_1608Metric
R14, R15: 3.3K; R_0603_1608Metric
R16: 3.3K; R_0603_1608Metric; not fitted
U4: ICM-40609-D

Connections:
/IMU_2/INT1: U4.12 (INT1/INT); also elsewhere on the board
/IMU_2/INT2/FSYNC: U4.19 (INT2/FSYNC); also elsewhere on the board
/IMU_2/MOSI: R15.2, U4.24 (SDA/SDI/SDIO); also elsewhere on the board
/IMU_2/SCLK: R14.2, U4.23 (SCL/SCLK); also elsewhere on the board
/IMU_2/SDO: R16.2, U4.9 (SDO/AD0); also elsewhere on the board
/IMU_2/nCS: R13.2, U4.22 (nCS); also elsewhere on the board
VDDIMU_1_IO: C40.1, FB3.1, R13.1, R14.1, R15.1, R16.1, U4.8 (VDDIO); also elsewhere on the board
VDDIMU_2: C38.2, C39.2, FB3.2, U4.13 (VDD)
